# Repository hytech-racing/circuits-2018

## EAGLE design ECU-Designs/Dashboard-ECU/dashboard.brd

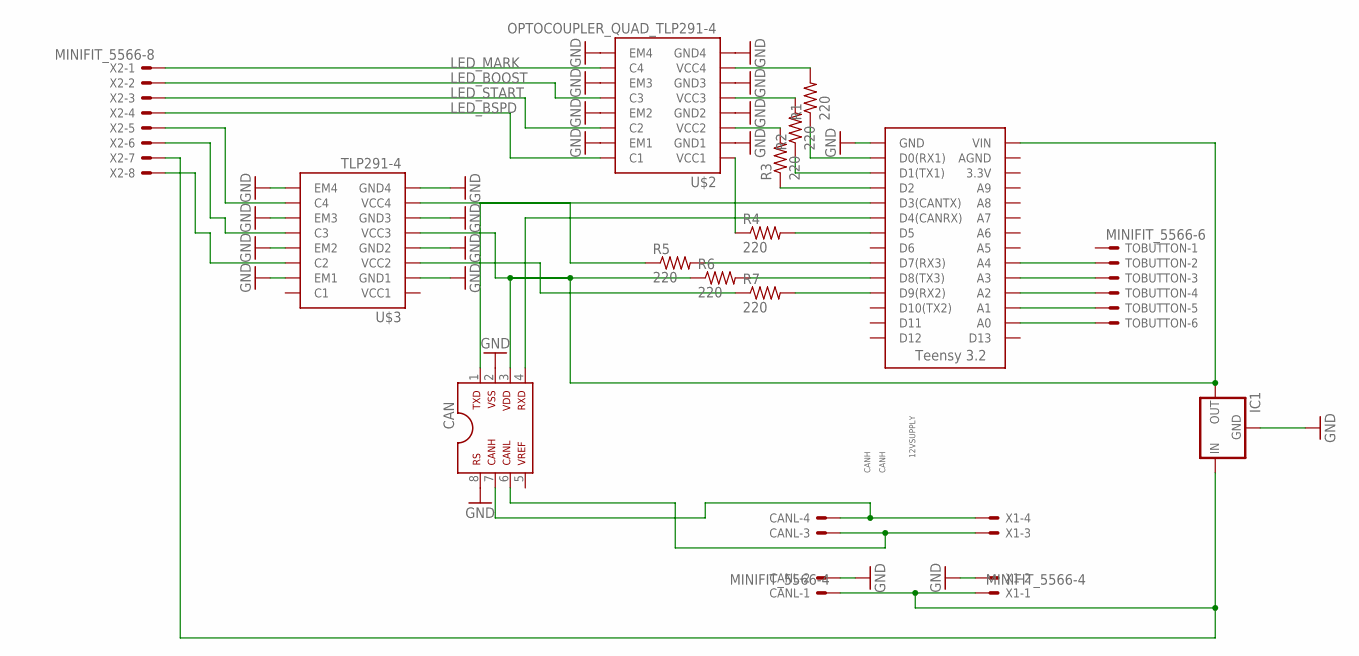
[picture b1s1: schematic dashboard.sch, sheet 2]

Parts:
CAN: MCP2551SOIC; SOIC08
CANL: MINIFIT_5566-4
IC1: 5V_REGULATOR_LM340-NLM340MPX-5.0/NOPB; SOT223
R1, R2, R3, R4, R5, R6, R7: 220; 0805
TOBUTTON: MINIFIT_5566-6
U$1: TEENSY_3.2_SIMPLE
U$2: OPTOCOUPLER_QUAD_TLP291-4; SO-16
U$3: TLP291-4; SOIC-16
X1: MINIFIT_5566-4
X2: MINIFIT_5566-8

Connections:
12VSUPPLY: CANL.1, IC1.1 (IN), X1.1, X2.7
BOOST: TOBUTTON.3, U$1.A3
BUZZER: U$3.14 (C2), X2.8
CANH: CAN.6, CANL.3, X1.3
CANL: CAN.7, CANL.4, X1.4
GND: CAN.2, CAN.8, CANL.2, IC1.2 (GND), IC1.4 (GND), U$1.GND, U$2.2 (GND1), U$2.4 (GND2), U$2.6 (GND3), U$2.8 (GND4), U$2.9 (EM4), U$2.11 (EM3), U$2.13 (EM2), U$2.15 (EM1), U$3.2 (GND1), U$3.4 (GND2), U$3.6 (GND3), U$3.8 (GND4), U$3.9 (EM4), U$3.11 (EM3), U$3.13 (EM2), U$3.15 (EM1), X1.2
LED_BMS: U$3.12 (C3), X2.6
LED_BOOST: U$2.12 (C3), X2.2
LED_BSPD: U$2.16 (C1), X2.4
LED_IMD: U$3.10 (C4), X2.5
LED_MARK: U$2.10 (C4), X2.1
LED_START: U$2.14 (C2), X2.3
MARK: TOBUTTON.2, U$1.A4
unnamed: R1.1, U$1.D0(RX1)
unnamed: CAN.1, U$1.D3(CANTX)
unnamed: CAN.4, U$1.D4(CANRX)
unnamed: R2.1, U$1.D1(TX1)
unnamed: R3.1, U$1.D2
unnamed: R5.1, U$3.7 (VCC4)
unnamed: R4.1, U$2.1 (VCC1)
unnamed: R4.2, U$1.D5
unnamed: R5.2, U$1.D7(RX3)
unnamed: R6.2, U$1.D8(TX3)
unnamed: R1.2, U$2.7 (VCC4)
unnamed: R2.2, U$2.5 (VCC3)
unnamed: R3.2, U$2.3 (VCC2)
unnamed: R7.2, U$1.D9(RX2)
unnamed: CAN.3, IC1.3 (OUT), R6.1, U$1.VIN, U$3.5 (VCC3)
unnamed: R7.1, U$3.3 (VCC2)
SELECT: TOBUTTON.6, U$1.A0
START: TOBUTTON.4, U$1.A2
TOGGLE: TOBUTTON.5, U$1.A1

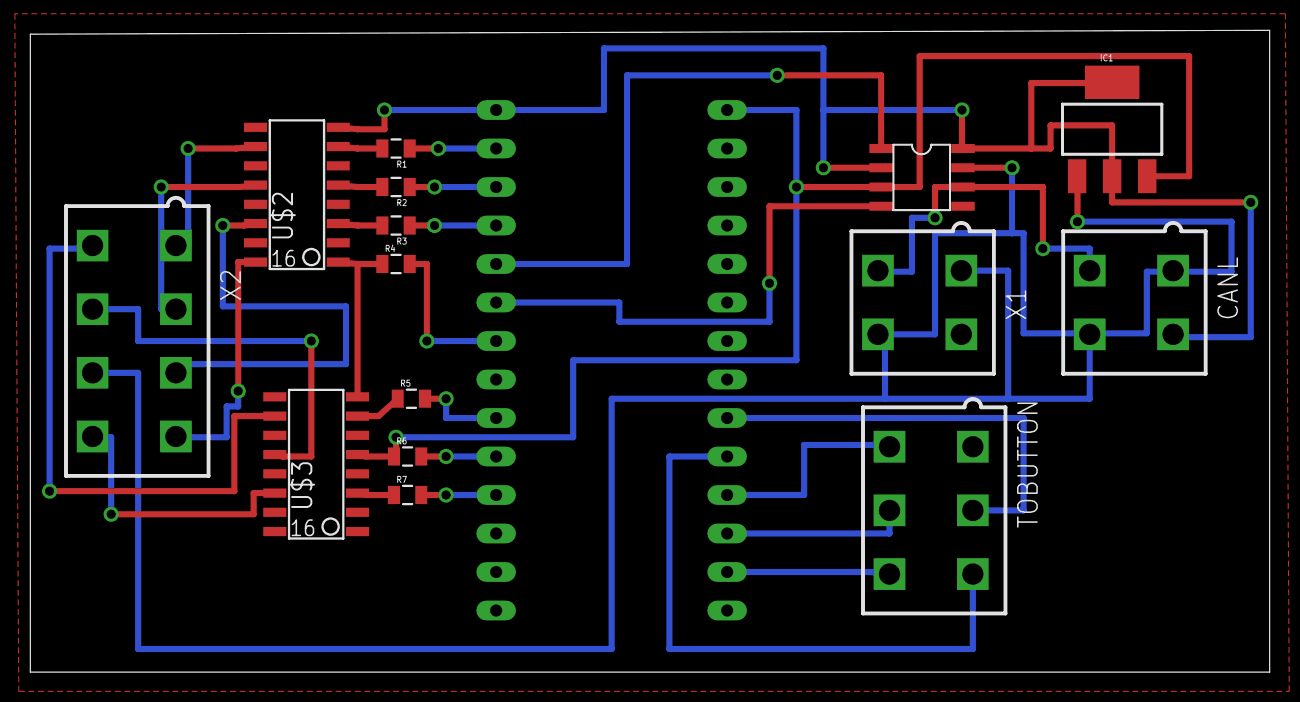
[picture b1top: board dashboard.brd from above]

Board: 2 copper layers, 81.8 x 42.3 mm, 16 parts (0 on the bottom side), 32 nets.

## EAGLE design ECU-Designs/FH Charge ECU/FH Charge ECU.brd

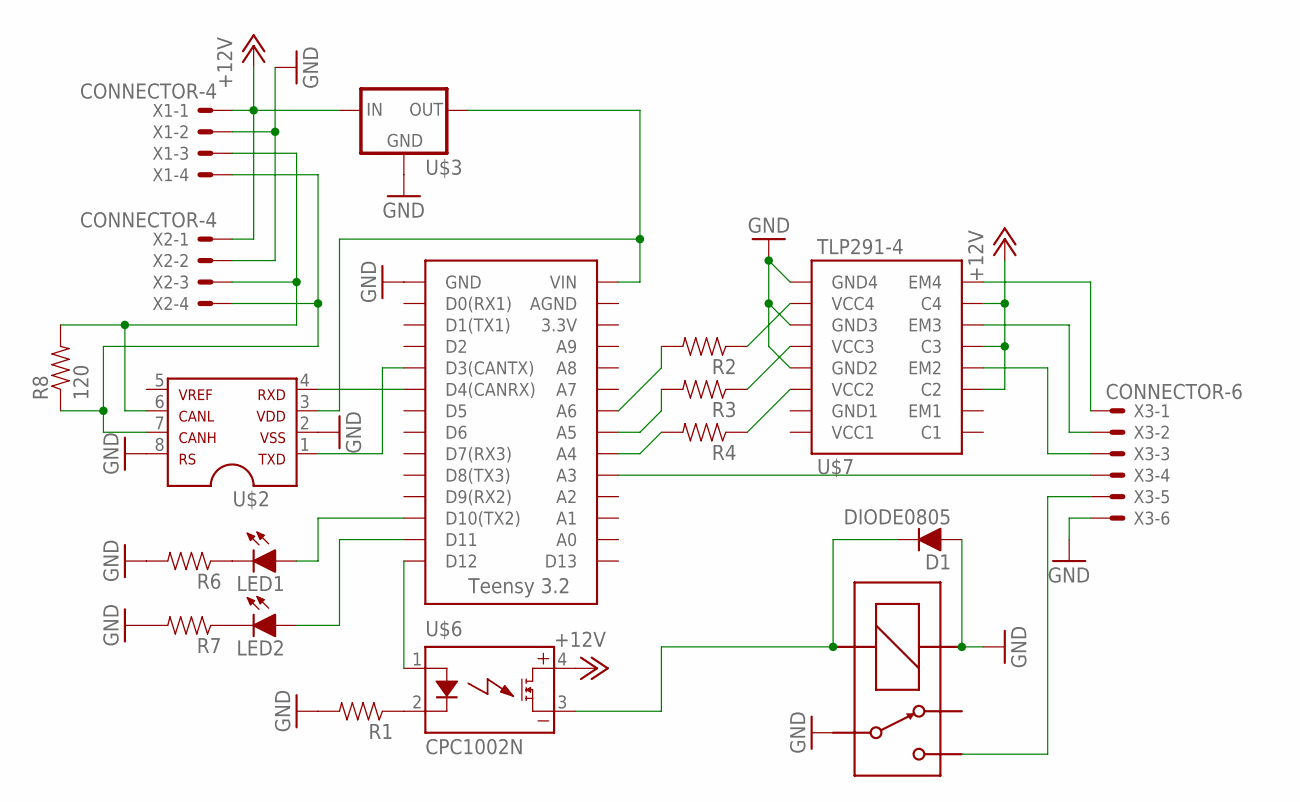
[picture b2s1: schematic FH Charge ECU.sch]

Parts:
D1: DIODE0805; 0805_D
LED1, LED2: LED-0805; LED-805
R1, R2, R3, R4, R6, R7: RESISTOR0805-RES; 0805
R8: 120; 0805
U$1: TEENSY_3.2_SIMPLE
U$2: MCP2551; SOIC-08
U$3: 5VREG_LM340-NLM340MPX-5.0/NOPB; SOT223
U$5: G5LE; ZF112
U$6: CPC1002N; SOP04
U$7: TLP291-4; SOIC-16
X1, X2: CONNECTOR-4; MINIFIT_5566-4
X3: CONNECTOR-6; MINIFIT_5566-6

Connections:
+12V: U$3.1 (IN), U$6.4 (DC+), U$7.10 (C4), U$7.12 (C3), U$7.14 (C2), X1.1, X2.1
GND: D1.A, R1.2, R6.2, R7.2, U$1.GND, U$2.2, U$2.8, U$3.2 (GND), U$3.4 (GND), U$5.1 (COIL+), U$5.P, U$7.4 (GND2), U$7.6 (GND3), U$7.8 (GND4), X1.2, X2.2, X3.6
unnamed: U$1.A3, X3.4
unnamed: U$1.VIN, U$2.3, U$3.3 (OUT)
unnamed: R8.2, U$2.6, X1.3, X2.3
unnamed: R8.1, U$2.7, X1.4, X2.4
unnamed: D1.C, U$5.2 (COIL-), U$6.3 (DC-)
unnamed: U$1.D3(CANTX), U$2.1
unnamed: U$1.D4(CANRX), U$2.4
unnamed: U$1.D12, U$6.1 (CONTROL+)
unnamed: R1.1, U$6.2 (CONTROL-)
unnamed: U$7.13 (EM2), X3.3
unnamed: U$5.S, X3.5
unnamed: U$7.11 (EM3), X3.2
unnamed: U$7.9 (EM4), X3.1
unnamed: R4.2, U$1.A4
unnamed: R3.2, U$1.A5
unnamed: R2.2, U$1.A6
unnamed: R3.1, U$7.5 (VCC3)
unnamed: R4.1, U$7.3 (VCC2)
unnamed: R2.1, U$7.7 (VCC4)
unnamed: LED1.C, R6.1
unnamed: LED2.C, R7.1
unnamed: LED1.A, U$1.D10(TX2)
unnamed: LED2.A, U$1.D11

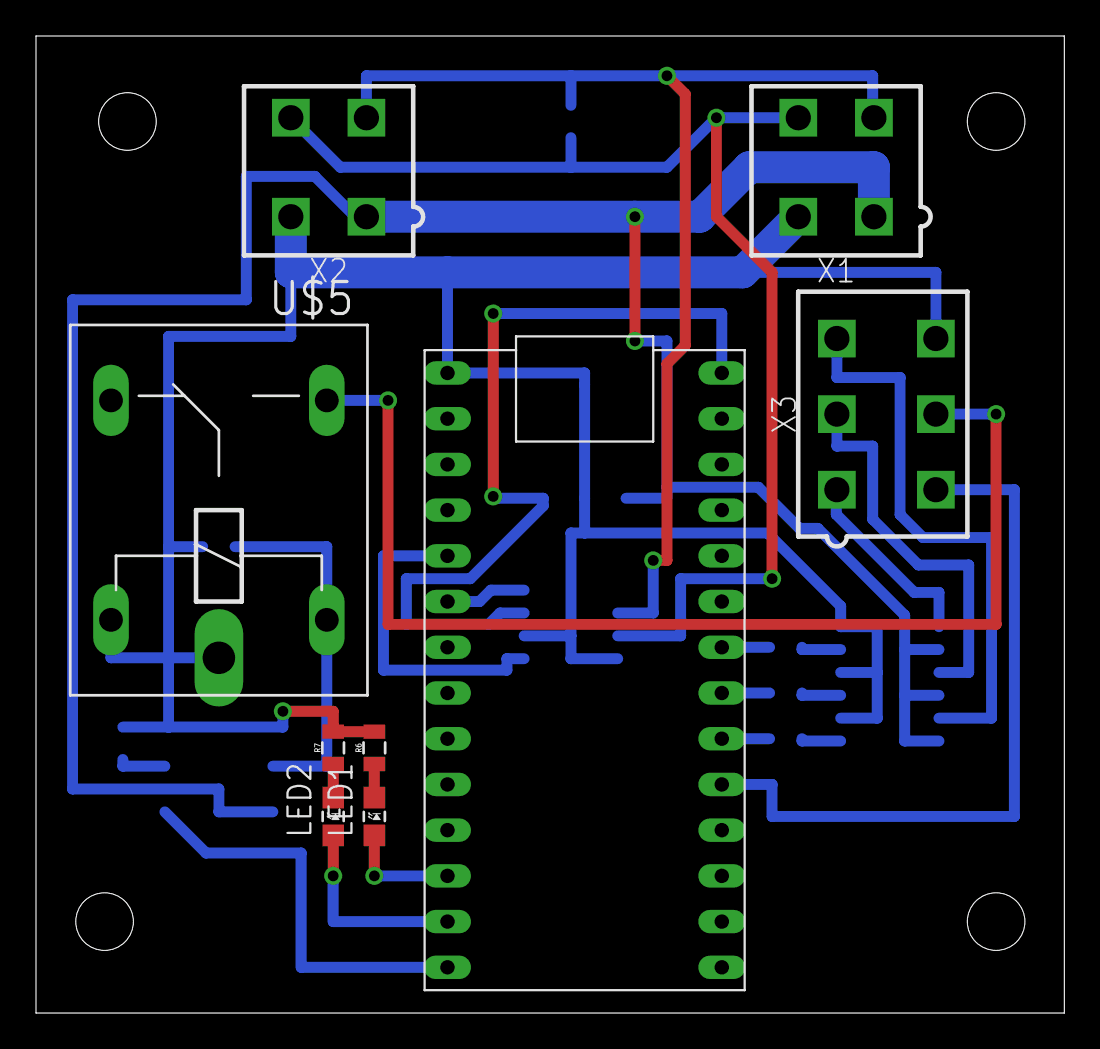
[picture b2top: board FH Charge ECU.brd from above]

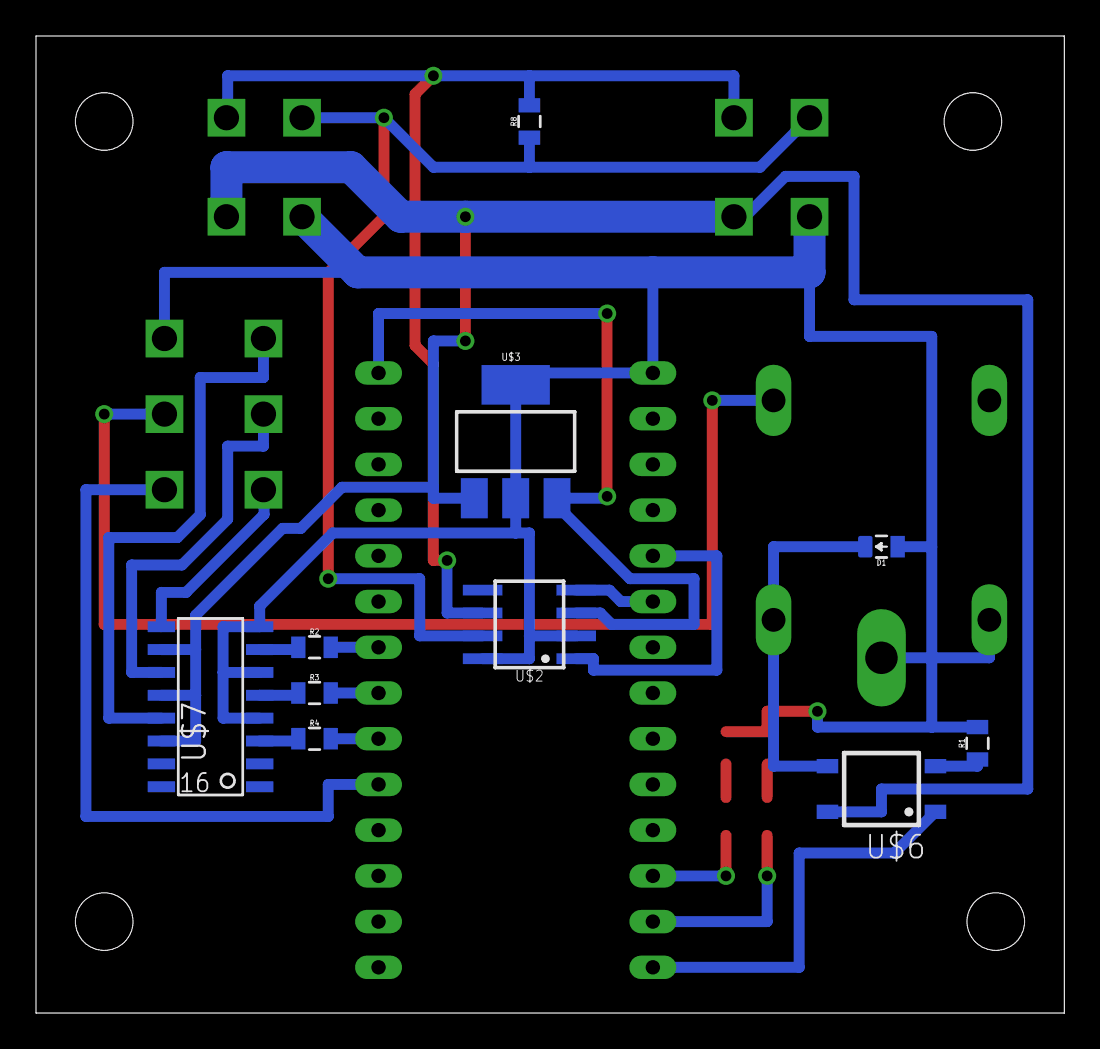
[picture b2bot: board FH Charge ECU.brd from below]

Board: 2 copper layers, 57.1 x 54.3 mm, 19 parts (10 on the bottom side), 25 nets.

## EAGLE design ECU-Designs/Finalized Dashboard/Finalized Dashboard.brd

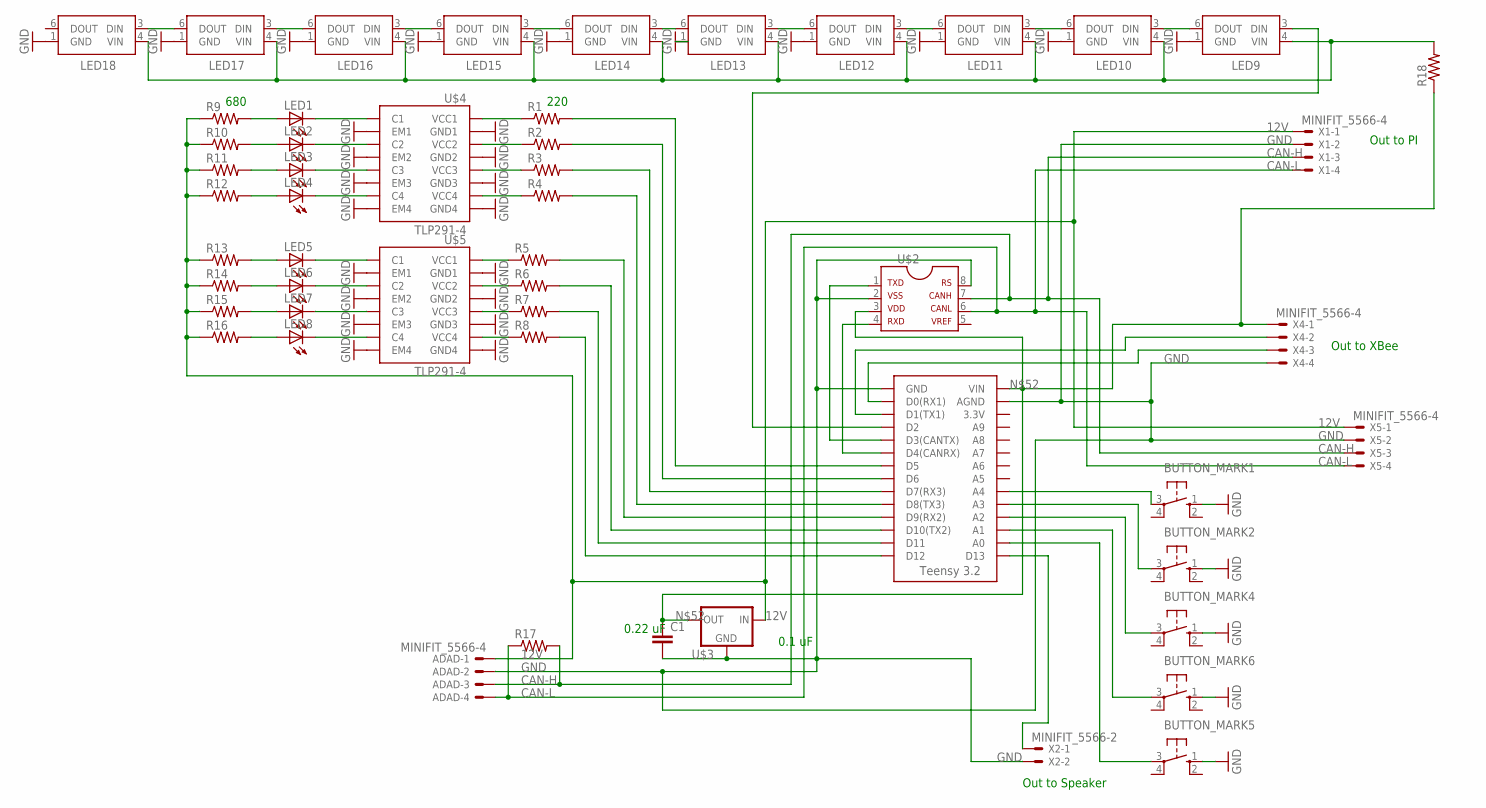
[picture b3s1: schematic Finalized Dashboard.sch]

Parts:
ADAD: MINIFIT_5566-4
BUTTON_MARK1, BUTTON_MARK2, BUTTON_MARK4, BUTTON_MARK5, BUTTON_MARK6: BTN_10-XX; B3F-10XX
C1: CAPEZ; CAP-PTH-SMALLEZ
LED1, LED2, LED3, LED4, LED5, LED6, LED7, LED8: LED-5MM
LED9, LED10, LED11, LED12, LED13, LED14, LED15, LED16, LED17, LED18: WS2812B5050; RGBLED5050
R1, R2, R3, R4, R5, R6, R7, R8, R9, R10, R11, R12, R13, R14, R15, R16, R17, R18: RESISTORAXIAL-0.3; AXIAL-0.3
U$1: TEENSY_3.2_SIMPLE
U$2: MCP2551; SOIC-08
U$3: 5V_REGULATOR_LM340-NLM340MPX-5.0/NOPB; SOT223
U$4, U$5: TLP291-4; SOIC-16
X1, X4, X5: MINIFIT_5566-4
X2: MINIFIT_5566-2

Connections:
5V: LED9.4 (VIN), LED10.4 (VIN), LED11.4 (VIN), LED12.4 (VIN), LED13.4 (VIN), LED14.4 (VIN), LED15.4 (VIN), LED16.4 (VIN), LED17.4 (VIN), LED18.4 (VIN), R18.P$2 (2)
12V: ADAD.1, R9.P$1 (1), R10.P$1 (1), R11.P$1 (1), R12.P$1 (1), R13.P$1 (1), R14.P$1 (1), R15.P$1 (1), R16.P$1 (1), U$3.1 (IN), X1.1, X5.1
CAN-H: ADAD.3, R17.P$2 (2), U$2.7, X1.3, X5.3
CAN-L: ADAD.4, R17.P$1 (1), U$2.6, X1.4, X5.4
GND: ADAD.2, BUTTON_MARK1.1 (S), BUTTON_MARK2.1 (S), BUTTON_MARK4.1 (S), BUTTON_MARK5.1 (S), BUTTON_MARK6.1 (S), C1.2, LED9.1 (GND), LED10.1 (GND), LED11.1 (GND), LED12.1 (GND), LED13.1 (GND), LED14.1 (GND), LED15.1 (GND), LED16.1 (GND), LED17.1 (GND), LED18.1 (GND), U$1.AGND, U$1.GND, U$2.2, U$2.8, U$3.2 (GND), U$3.4 (GND), U$4.2 (GND1), U$4.4 (GND2), U$4.6 (GND3), U$4.8 (GND4), U$4.9 (EM4), U$4.11 (EM3), U$4.13 (EM2), U$4.15 (EM1), U$5.2 (GND1), U$5.4 (GND2), U$5.6 (GND3), U$5.8 (GND4), U$5.9 (EM4), U$5.11 (EM3), U$5.13 (EM2), U$5.15 (EM1), X1.2, X2.2, X4.4, X5.2
unnamed: LED9.6 (DOUT), LED10.3 (DIN)
unnamed: U$1.D1(TX1), X4.2
unnamed: LED10.6 (DOUT), LED11.3 (DIN)
unnamed: LED11.6 (DOUT), LED12.3 (DIN)
unnamed: R1.P$1 (1), U$4.1 (VCC1)
unnamed: LED13.6 (DOUT), LED14.3 (DIN)
unnamed: R2.P$1 (1), U$4.3 (VCC2)
unnamed: R3.P$1 (1), U$4.5 (VCC3)
unnamed: U$1.D3(CANTX), U$2.1
unnamed: U$1.D4(CANRX), U$2.4
unnamed: R4.P$1 (1), U$4.7 (VCC4)
unnamed: R5.P$1 (1), U$5.1 (VCC1)
unnamed: U$1.D0(RX1), X4.3
unnamed: R6.P$1 (1), U$5.3 (VCC2)
unnamed: R7.P$1 (1), U$5.5 (VCC3)
unnamed: R8.P$1 (1), U$5.7 (VCC4)
unnamed: R1.P$2 (2), U$1.D5
unnamed: LED12.6 (DOUT), LED13.3 (DIN)
unnamed: R3.P$2 (2), U$1.D7(RX3)
unnamed: R4.P$2 (2), U$1.D8(TX3)
unnamed: R5.P$2 (2), U$1.D9(RX2)
unnamed: R6.P$2 (2), U$1.D10(TX2)
unnamed: R7.P$2 (2), U$1.D11
unnamed: R8.P$2 (2), U$1.D12
unnamed: LED1.A, R9.P$2 (2)
unnamed: LED2.A, R10.P$2 (2)
unnamed: LED3.A, R11.P$2 (2)
unnamed: LED4.A, R12.P$2 (2)
unnamed: LED5.A, R13.P$2 (2)
unnamed: LED6.A, R14.P$2 (2)
unnamed: LED7.A, R15.P$2 (2)
unnamed: LED8.A, R16.P$2 (2)
unnamed: LED1.K (C), U$4.16 (C1)
unnamed: LED2.K (C), U$4.14 (C2)
unnamed: LED3.K (C), U$4.12 (C3)
unnamed: LED4.K (C), U$4.10 (C4)
unnamed: LED5.K (C), U$5.16 (C1)
unnamed: LED6.K (C), U$5.14 (C2)
unnamed: LED7.K (C), U$5.12 (C3)
unnamed: LED8.K (C), U$5.10 (C4)
unnamed: U$1.D13, X2.1
unnamed: BUTTON_MARK1.3, U$1.A4
unnamed: BUTTON_MARK2.3, U$1.A3
unnamed: BUTTON_MARK4.3, U$1.A2
unnamed: BUTTON_MARK6.3, U$1.A1
unnamed: BUTTON_MARK5.3, U$1.A0
unnamed: R2.P$2 (2), U$1.D6
unnamed: LED14.6 (DOUT), LED15.3 (DIN)
unnamed: LED15.6 (DOUT), LED16.3 (DIN)
unnamed: LED16.6 (DOUT), LED17.3 (DIN)
unnamed: LED17.6 (DOUT), LED18.3 (DIN)
unnamed: C1.1, R18.P$1 (1), U$1.VIN, U$2.3, U$3.3 (OUT), X4.1
unnamed: LED9.3 (DIN), U$1.D2

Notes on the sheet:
680
220
0.22 uF
0.1 uF
Out to PI
Out to Speaker
Out to XBee

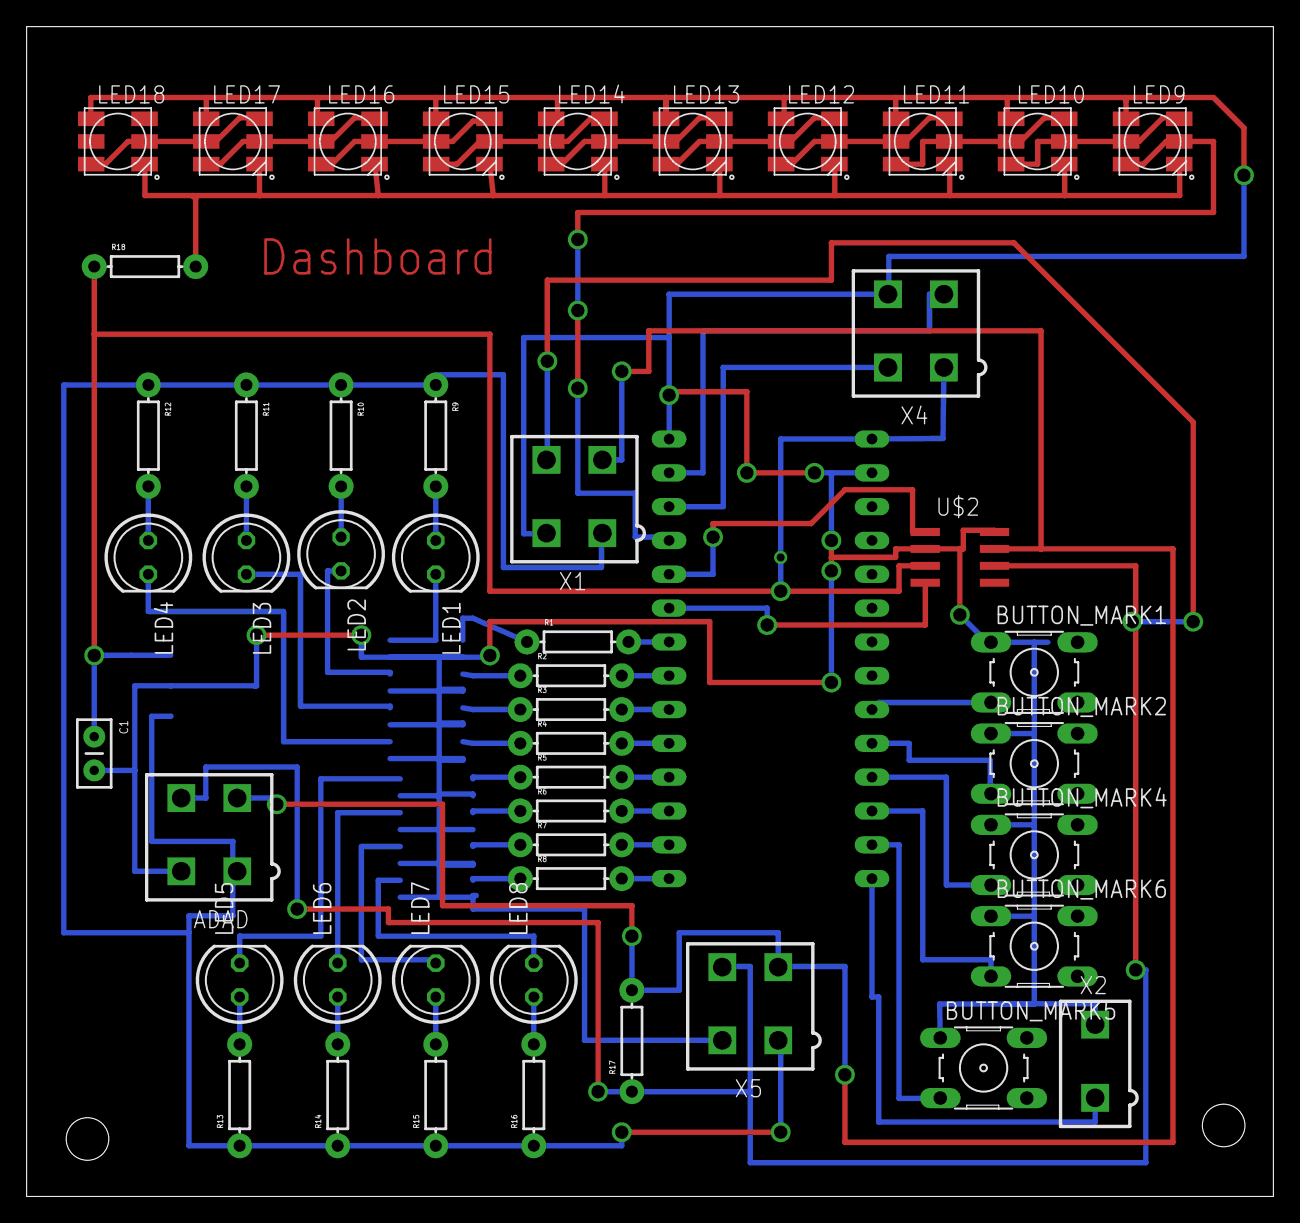
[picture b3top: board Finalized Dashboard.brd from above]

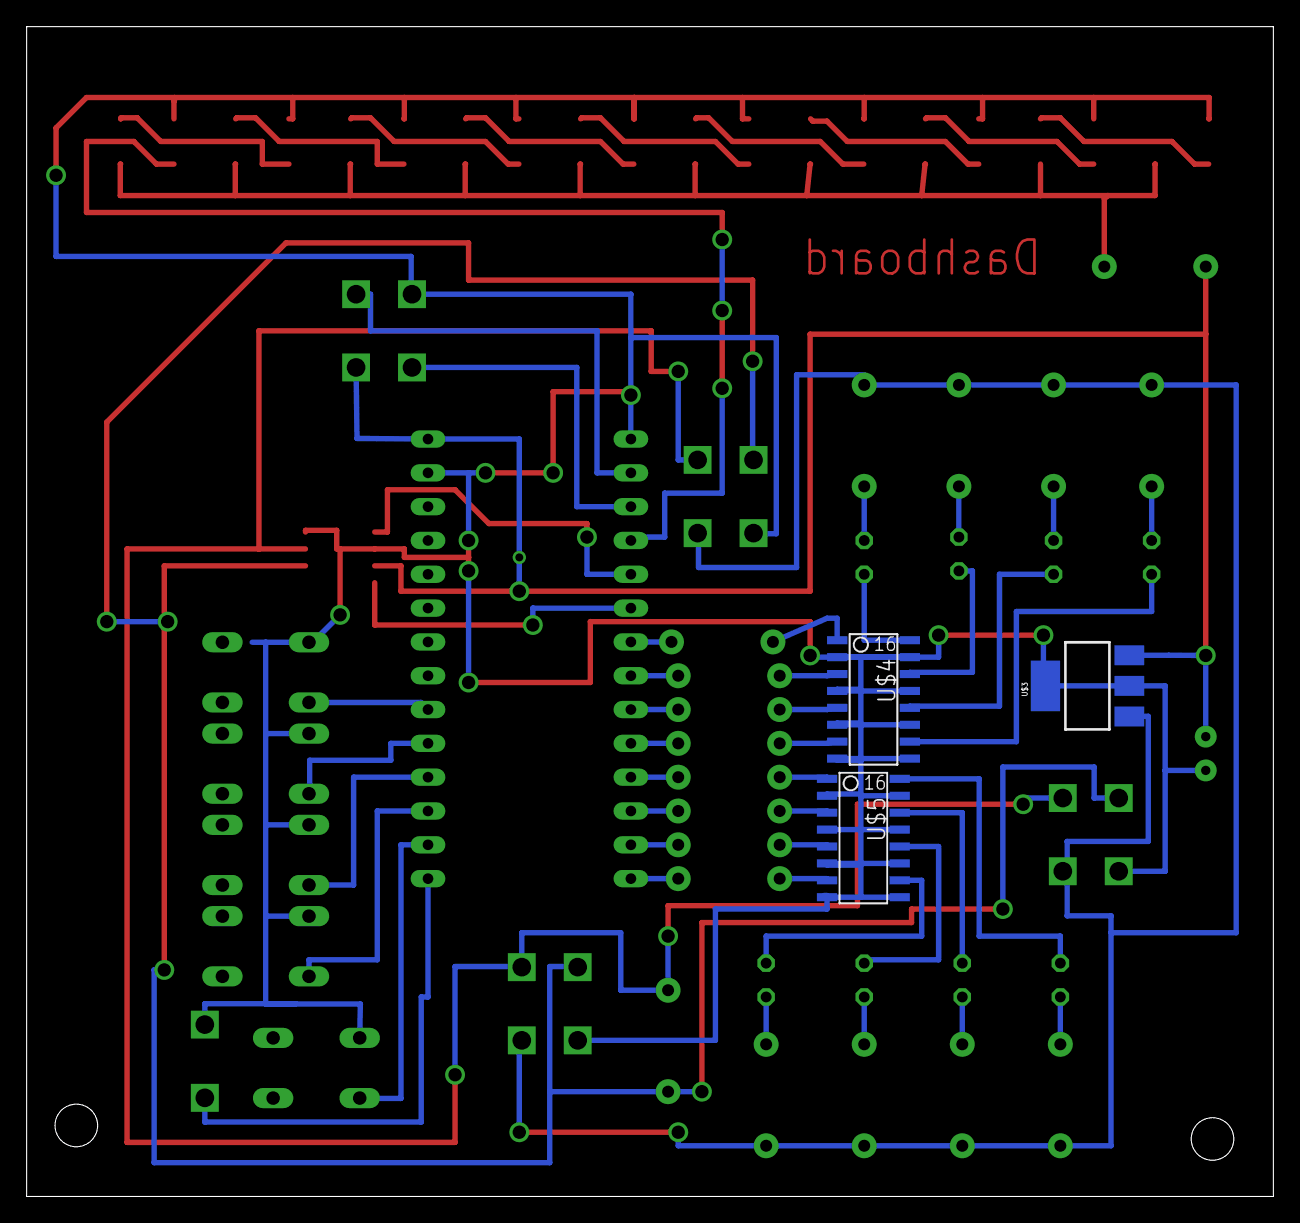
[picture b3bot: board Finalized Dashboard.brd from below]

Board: 2 copper layers, 93.7 x 87.9 mm, 52 parts (3 on the bottom side), 58 nets.

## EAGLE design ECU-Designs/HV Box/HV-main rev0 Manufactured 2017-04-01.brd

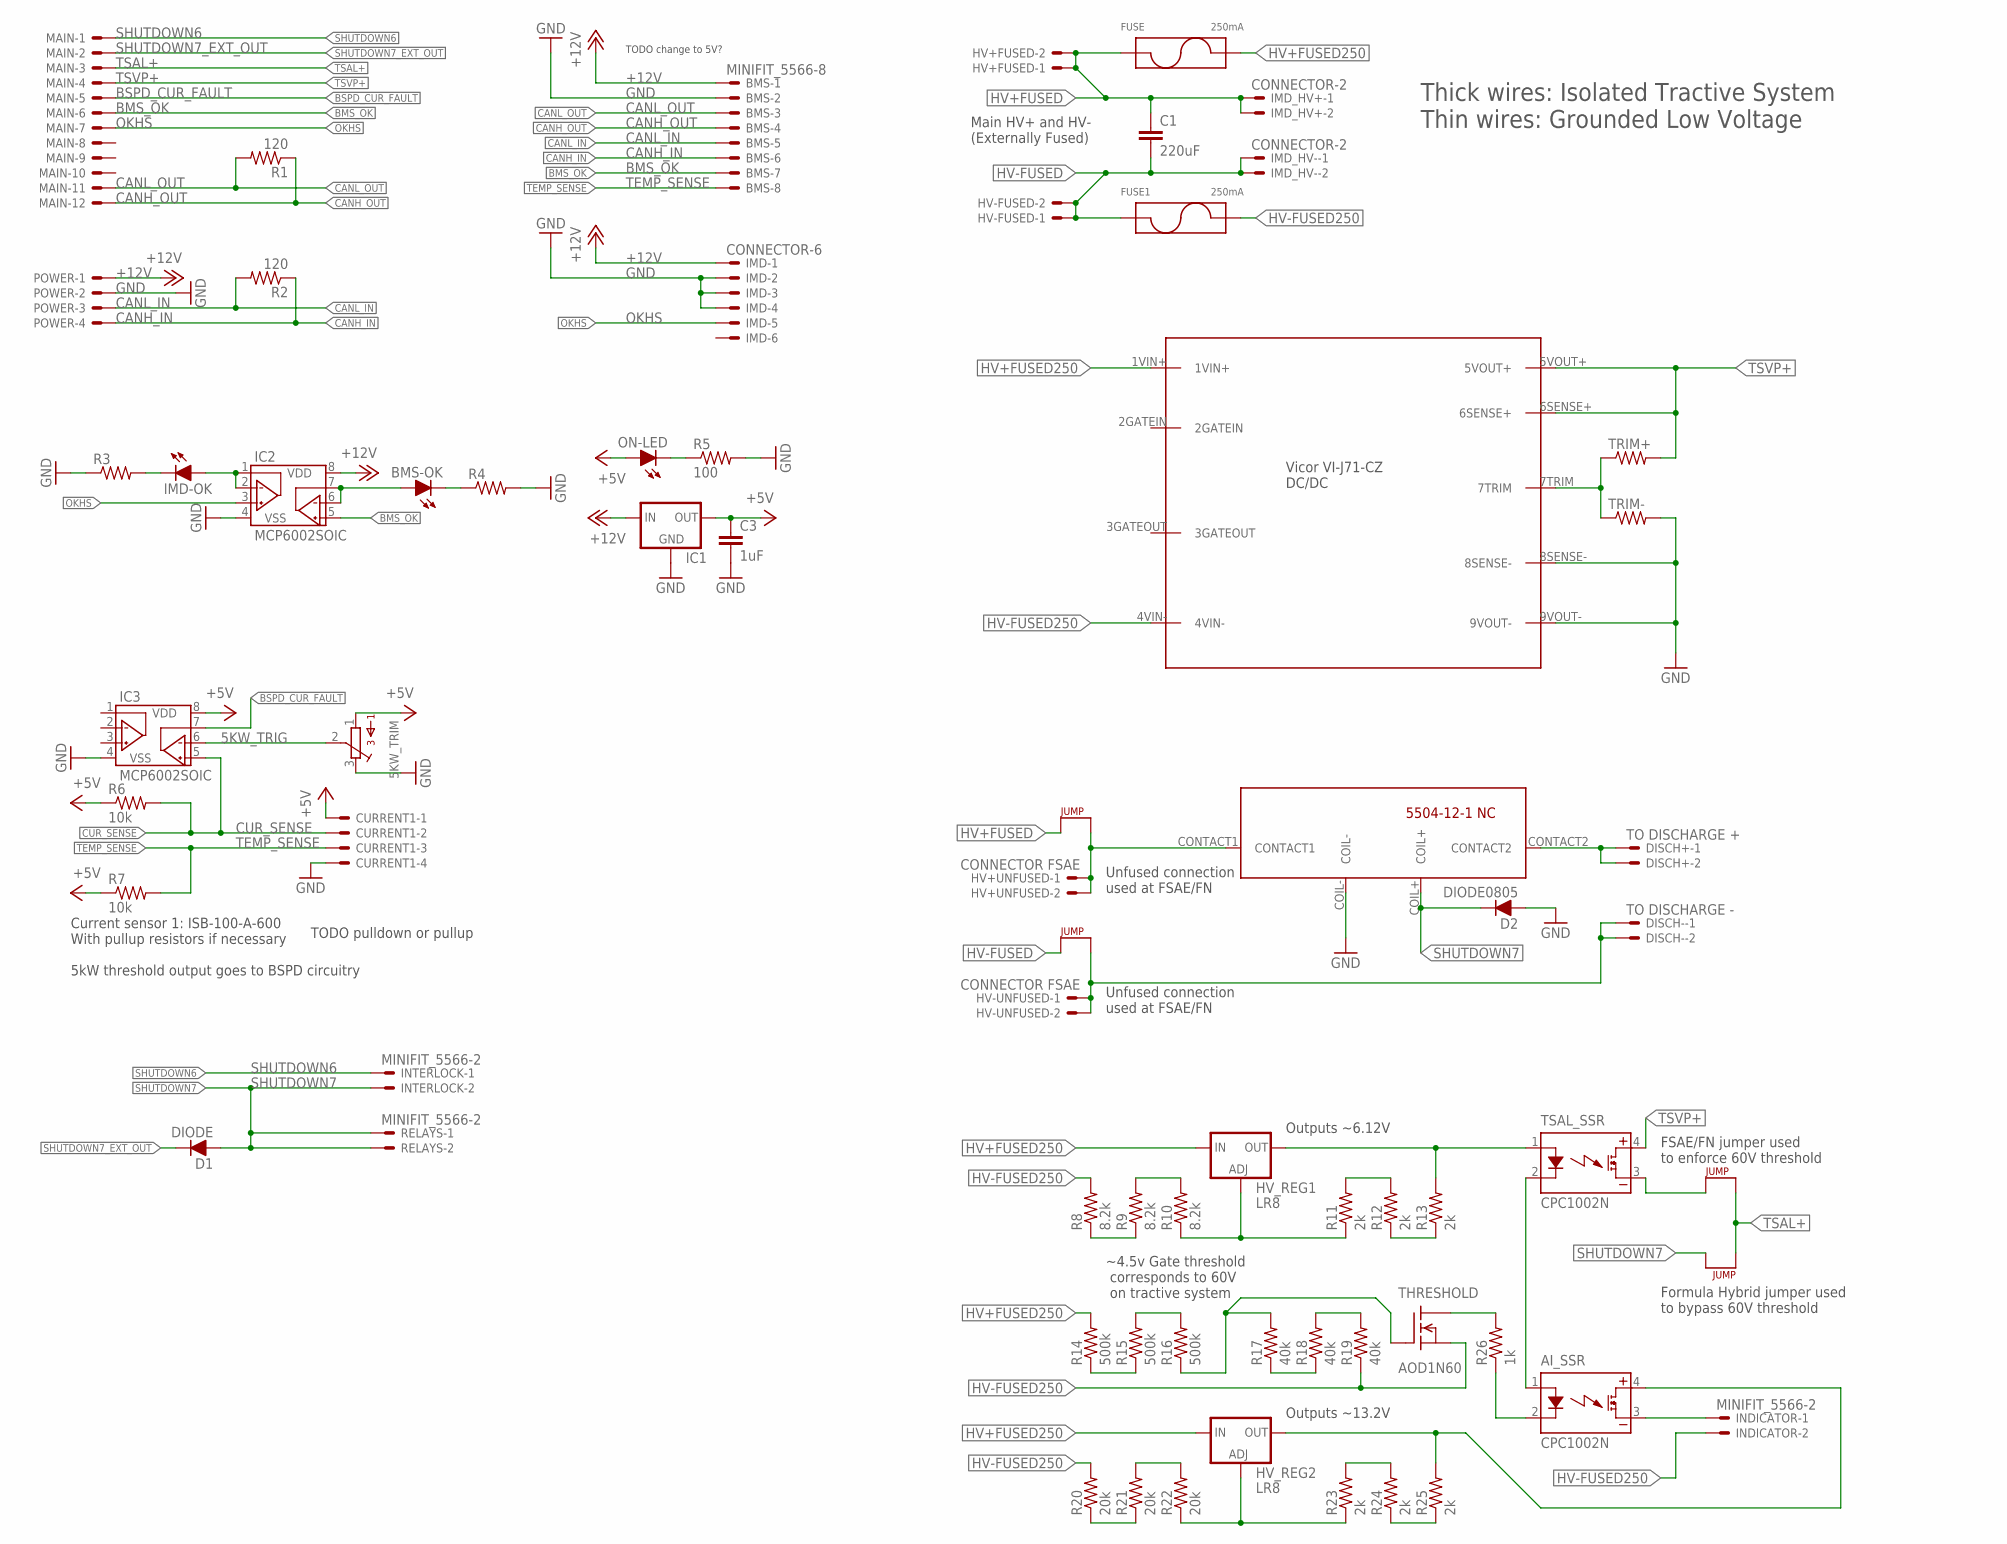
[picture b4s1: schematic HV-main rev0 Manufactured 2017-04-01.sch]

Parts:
5KW_TRIM: TRIMPOT_3296C; TRIMPOT_3296
AI_SSR: CPC1002N; SOP04
BMS: MINIFIT_5566-8
BMS-OK: LED-0805; LED-805
C1: 220uF; LLS2V221MELZ
C3: 1uF; 0805
CURRENT1: MINIFIT_5566-4
D1: DIODE; DO-41
D2: DIODE0805; 0805_D
DISCH+: TO DISCHARGE +; MINIFIT_5566-2
DISCH-: TO DISCHARGE -; MINIFIT_5566-2
FUSE, FUSE1: 250mA; 1A3400_38.1MM
HV+FUSED: MINIFIT_5566-2
HV+UNFUSED: CONNECTOR FSAE; MINIFIT_5566-2
HV-FUSED: MINIFIT_5566-2
HV-UNFUSED: CONNECTOR FSAE; MINIFIT_5566-2
HV_REG1, HV_REG2: LR8; TO-252
IC1: 5VREG_L7805_VERT; TO-220
IC2, IC3: MCP6002SOIC; SOIC-08
IMD: CONNECTOR-6; MINIFIT_5566-6
IMD-OK: LED-0805; LED-805
IMD_HV+: CONNECTOR-2; MINIFIT_5566-2
IMD_HV-: CONNECTOR-2; MINIFIT_5566-2
INDICATOR: MINIFIT_5566-2
INTERLOCK: MINIFIT_5566-2
MAIN: CONNECTOR-12; MINIFIT_5566-12
ON-LED: LED-0805; LED-805
POWER: MINIFIT_5566-4
R1, R2: 120; 0805
R3, R4: RESISTOR0805-RES; 0805
R5: 100; 0805
R6, R7: 10k; 0805
R8, R9, R10: 8.2k; 0805
R11, R12, R13, R23, R24, R25: 2k; 0805
R14, R15, R16: 500k; 0805
R17, R18, R19: 40k; 0805
R20, R21, R22: 20k; 0805
R26: 1k; 0805
RELAYS: MINIFIT_5566-2
THRESHOLD: AOD1N60; TO-252
TRIM+: RESISTOR0805-RES; 0805
TRIM-: RESISTOR0805-RES; 0805
TSAL_SSR: CPC1002N; SOP04
U$1, U$2, U$3, U$4: JUMPER.3; AXIAL-0.3
U$5: HV_DCDC_VI-J71-CZ
U$12: 5504-12-1-NC

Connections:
5KW_TRIG: 5KW_TRIM.2, IC3.6 (VINB-)
+5V: 5KW_TRIM.1, C3.1, CURRENT1.1, IC1.3 (OUT), IC3.8 (VDD), ON-LED.A, R6.1, R7.1
+12V: BMS.1, IC1.1 (IN), IC2.8 (VDD), IMD.1, POWER.1
BMS_OK: BMS.7, IC2.5 (VINB+), MAIN.6
BSPD_CUR_FAULT: IC3.7 (VOUTB), MAIN.5
CANH_IN: BMS.6, POWER.4, R2.1
CANH_OUT: BMS.4, MAIN.12, R1.1
CANL_IN: BMS.5, POWER.3, R2.2
CANL_OUT: BMS.3, MAIN.11, R1.2
CUR_SENSE: CURRENT1.2, IC3.5 (VINB+), R6.2
DISCHARGE1: HV+UNFUSED.1, HV+UNFUSED.2, U$3.P$2, U$12.CONTACT1
DISCHARGE2: DISCH+.1, DISCH+.2, U$12.CONTACT2
DISCHARGE3: DISCH-.1, DISCH-.2, HV-UNFUSED.1, HV-UNFUSED.2, U$4.P$2
GND: 5KW_TRIM.3, BMS.2, C3.2, CURRENT1.4, D2.A, IC1.2 (GND), IC2.4 (VSS), IC3.4 (VSS), IMD.2, IMD.3, IMD.4, POWER.2, R3.1, R4.2, R5.2, TRIM-.2, U$5.8SENSE-, U$5.9VOUT-, U$12.COIL-
HV+FUSED: C1.P$1 (1), FUSE.P1, FUSE.P2 (P1), HV+FUSED.1, HV+FUSED.2, IMD_HV+.1, IMD_HV+.2, U$3.P$1
HV+FUSED250: FUSE.N3 (P2), FUSE.N4 (P2), HV_REG1.1 (IN), HV_REG2.1 (IN), R14.2, U$5.1VIN+
HV-FUSED: C1.P$2 (2), FUSE1.P1, FUSE1.P2 (P1), HV-FUSED.1, HV-FUSED.2, IMD_HV-.1, IMD_HV-.2, U$4.P$1
HV-FUSED250: FUSE1.N3 (P2), FUSE1.N4 (P2), INDICATOR.2, R8.2, R19.1, R20.2, THRESHOLD.3 (S), U$5.4VIN-
unnamed: AI_SSR.4 (DC+), HV_REG2.2(TAB) (OUT), R25.2
unnamed: HV_REG1.2(TAB) (OUT), R13.2, TSAL_SSR.1 (CONTROL+)
unnamed: ON-LED.C, R5.1
unnamed: TSAL_SSR.3 (DC-), U$1.P$1
unnamed: AI_SSR.2 (CONTROL-), R26.1
unnamed: AI_SSR.1 (CONTROL+), TSAL_SSR.2 (CONTROL-)
unnamed: AI_SSR.3 (DC-), INDICATOR.1
unnamed: R8.1, R9.1
unnamed: R26.2, THRESHOLD.2(TAB) (D)
unnamed: R14.1, R15.1
unnamed: R15.2, R16.2
unnamed: R17.1, R18.1
unnamed: R18.2, R19.2
unnamed: R9.2, R10.2
unnamed: HV_REG2.3 (ADJ), R22.1, R23.1
unnamed: R11.2, R12.2
unnamed: R12.1, R13.1
unnamed: HV_REG1.3 (ADJ), R10.1, R11.1
unnamed: R23.2, R24.2
unnamed: R24.1, R25.1
unnamed: R21.2, R22.2
unnamed: R16.1, R17.2, THRESHOLD.1 (G)
unnamed: R20.1, R21.1
unnamed: IC2.1 (VOUTA), IC2.2 (VINA-), IMD-OK.A
unnamed: BMS-OK.A, IC2.6 (VINB-), IC2.7 (VOUTB)
unnamed: BMS-OK.C, R4.1
unnamed: IMD-OK.C, R3.2
OKHS: IC2.3 (VINA+), IMD.5, MAIN.7
SHUTDOWN6: INTERLOCK.1, MAIN.1
SHUTDOWN7: D1.A, D2.C, INTERLOCK.2, RELAYS.1, RELAYS.2, U$2.P$2, U$12.COIL+
SHUTDOWN7_EXT_OUT: D1.C, MAIN.2
TEMP_SENSE: BMS.8, CURRENT1.3, R7.2
TRIM: TRIM+.1, TRIM-.1, U$5.7TRIM
TSAL+: MAIN.3, U$1.P$2, U$2.P$1
TSVP+: MAIN.4, TRIM+.2, TSAL_SSR.4 (DC+), U$5.5VOUT+, U$5.6SENSE+

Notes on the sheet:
Formula Hybrid jumper used to bypass 60V threshold
Current sensor 1: ISB-100-A-600 With pullup resistors if necessary 5kW threshold output goes to BSPD circuitry
Unfused connection used at FSAE/FN
FSAE/FN jumper used to enforce 60V threshold
Main HV+ and HV- (Externally Fused)
TODO pulldown or pullup
TODO change to 5V?
~4.5v Gate threshold corresponds to 60V on tractive system
Thick wires: Isolated Tractive System Thin wires: Grounded Low Voltage
Outputs ~6.12V
Outputs ~13.2V

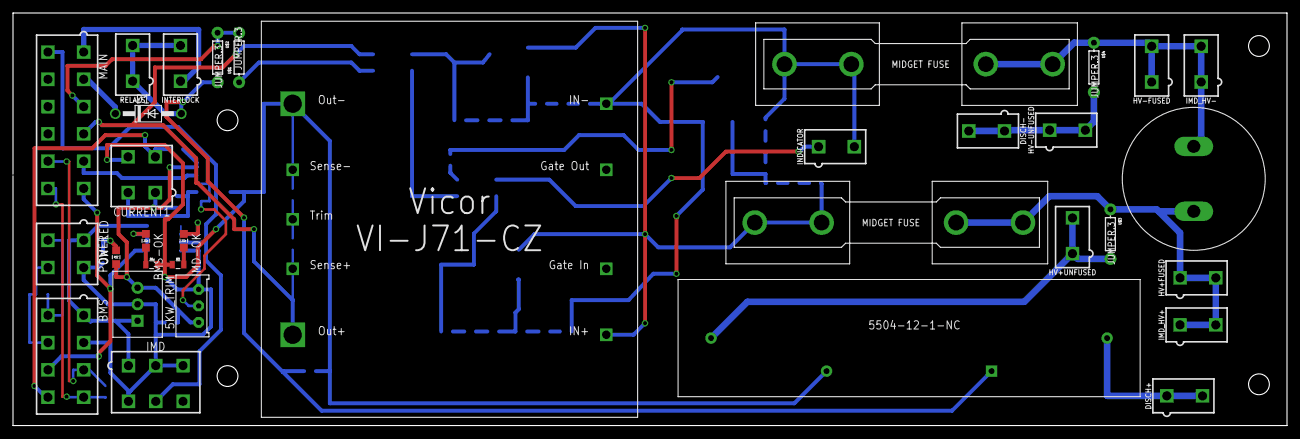
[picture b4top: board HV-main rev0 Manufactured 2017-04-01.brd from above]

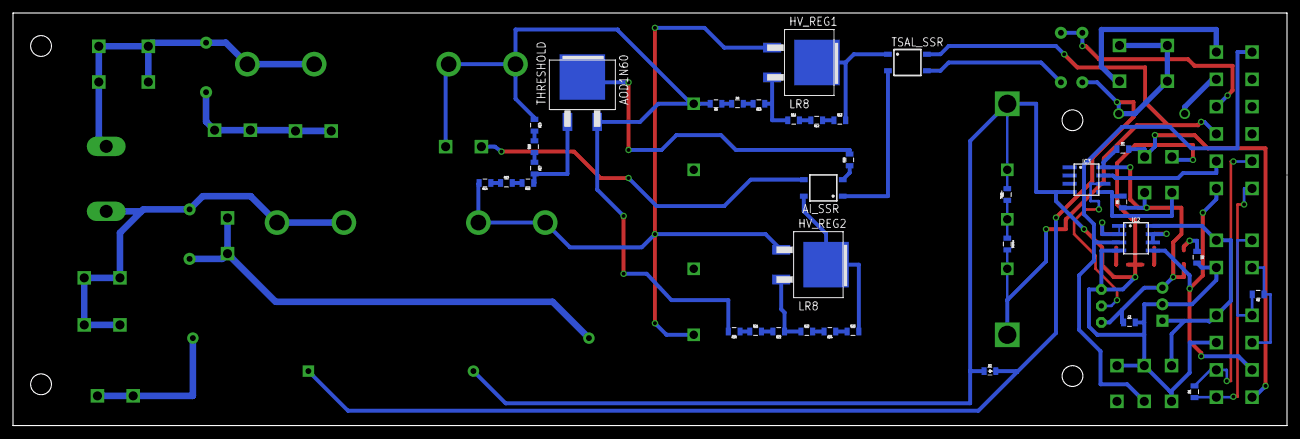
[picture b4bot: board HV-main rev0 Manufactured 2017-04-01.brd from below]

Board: 2 copper layers, 196.1 x 63.5 mm, 68 parts (35 on the bottom side), 53 nets.

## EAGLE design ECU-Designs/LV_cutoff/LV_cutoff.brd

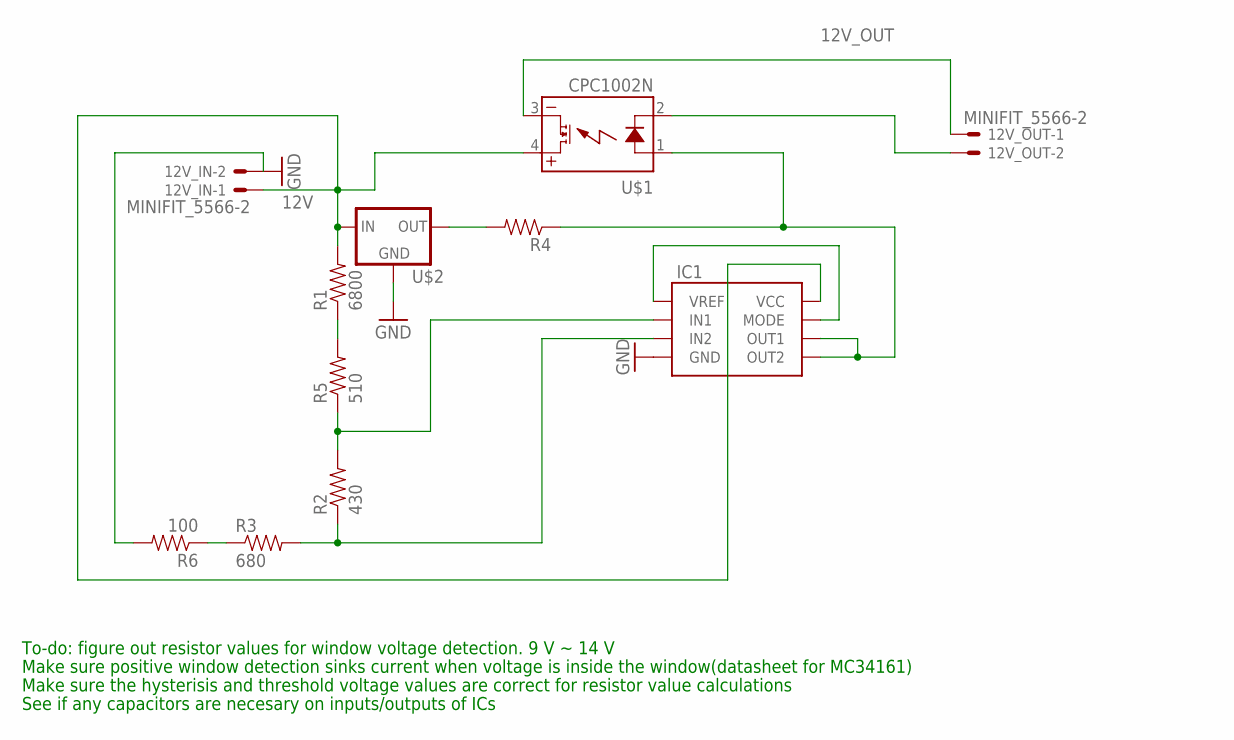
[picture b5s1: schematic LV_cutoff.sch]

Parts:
12V_IN, 12V_OUT: MINIFIT_5566-2
IC1: MC34161DG; SOIC-08
R1: 6800; 0805
R2: 430; 0805
R3: 680; 0805
R4: RESISTOR0805-RES; 0805
R5: 510; 0805
R6: 100; 0805
U$1: CPC1002N; SOP04
U$2: 5VREG_LM340-NLM340MPX-5.0/NOPB; SOT223

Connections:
12V: 12V_IN.1, IC1.8 (VCC), R1.2, U$1.4 (DC+), U$2.1 (IN)
12V_OUT: 12V_OUT.1, U$1.3 (DC-)
GND: 12V_IN.2, IC1.4 (GND), R6.2, U$2.2 (GND), U$2.4 (GND)
unnamed: IC1.5 (OUT2), IC1.6 (OUT1), R4.1, U$1.1 (CONTROL+)
unnamed: IC1.1 (VREF), IC1.7 (MODE)
unnamed: R4.2, U$2.3 (OUT)
unnamed: IC1.2 (IN1), R2.2, R5.1
unnamed: IC1.3 (IN2), R2.1, R3.2
unnamed: 12V_OUT.2, U$1.2 (CONTROL-)
unnamed: R3.1, R6.1
unnamed: R1.1, R5.2

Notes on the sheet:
To-do: figure out resistor values for window voltage detection. 9 V ~ 14 V
Make sure the hysterisis and threshold voltage values are correct for resistor value calculations
Make sure positive window detection sinks current when voltage is inside the window(datasheet for MC34161)
See if any capacitors are necesary on inputs/outputs of ICs

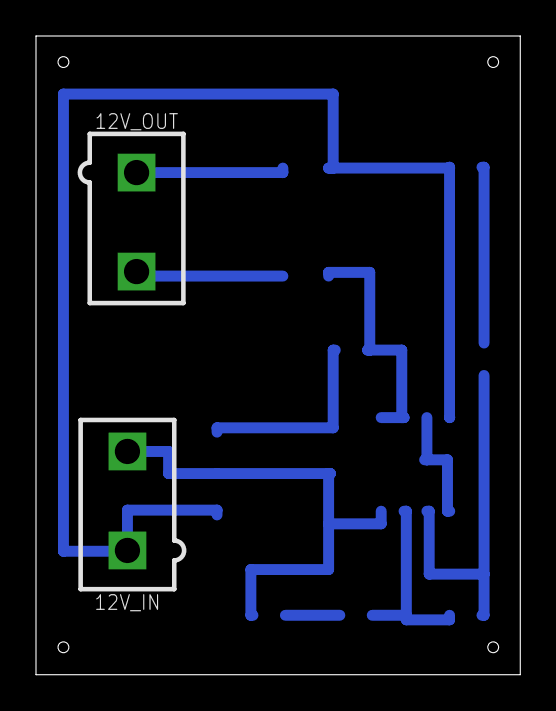
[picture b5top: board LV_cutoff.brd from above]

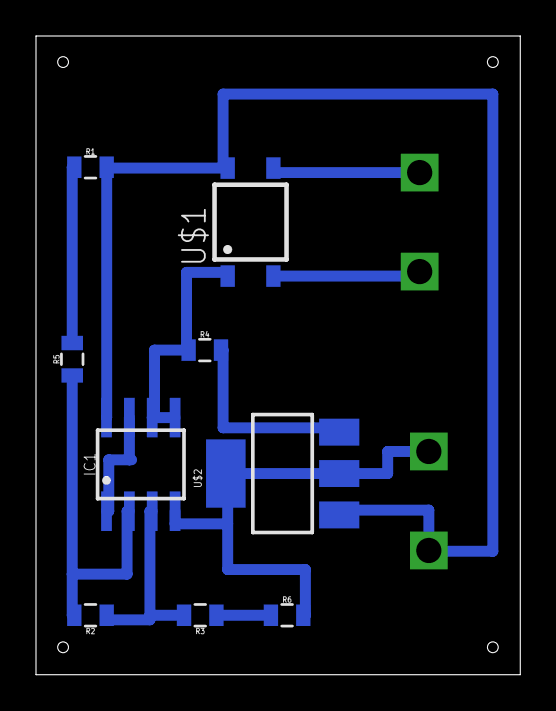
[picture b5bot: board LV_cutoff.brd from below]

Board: 2 copper layers, 26.9 x 35.5 mm, 11 parts (9 on the bottom side), 11 nets.
